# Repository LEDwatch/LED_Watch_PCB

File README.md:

# LED_Watch_PCB
LED Wrist Watch schematic and circuit board files

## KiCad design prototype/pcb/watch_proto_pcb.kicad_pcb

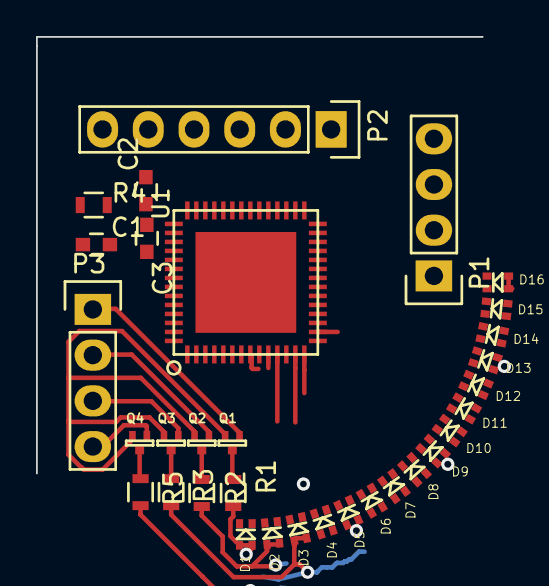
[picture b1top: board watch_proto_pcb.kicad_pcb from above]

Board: 2 copper layers, 32 parts (0 on the bottom side), 27 nets.

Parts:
C1, C2, C3: C; C_0603
D1, D2, D3, D4, D5, D6, D7, D8, D9, D10, D11, D12, D13, D14, D15, D16: APHB1608LVBDSEKJ3C; led_dual
P1, P3: CONN_01X04; Pin_Header_Straight_1x04
P2: CONN_01X06; Pin_Header_Straight_1x06
Q1, Q2, Q3, Q4: RZM001P02; SOT-723-3
R1, R2, R3, R4, R5: R; R_0603
U1: TLC5954; QFN_N56_THERM

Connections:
/proto_TLC/B0: D1.1, D2.1, D3.1, D4.1, U1.10
/proto_TLC/B1: D5.1, D6.1, D7.1, D8.1, U1.13
/proto_TLC/B2: D9.1, D10.1, D11.1, D12.1, U1.16
/proto_TLC/B3: D13.1, D14.1, D15.1, D16.1, U1.19
/proto_TLC/BLANK: P1.4, U1.29
/proto_TLC/LAT: P1.2, U1.27
/proto_TLC/LED_EN_0: P3.1, Q1.1
/proto_TLC/LED_EN_1: P3.2, Q2.1
/proto_TLC/LED_EN_2: P3.3, Q3.1
/proto_TLC/LED_EN_3: P3.4, Q4.1
/proto_TLC/LED_MOS_0: Q1.3, R1.1
/proto_TLC/LED_MOS_1: Q2.3, R2.1
/proto_TLC/LED_MOS_2: Q3.3, R3.1
/proto_TLC/LED_MOS_3: Q4.3, R5.1
/proto_TLC/LED_PWR_OUT_0: D1.2, D1.4, D5.2, D5.4, D9.2, D9.4, D13.2, D13.4, R1.2
/proto_TLC/LED_PWR_OUT_1: D2.2, D2.4, D6.2, D6.4, D10.2, D10.4, D14.2, D14.4, R2.2
/proto_TLC/LED_PWR_OUT_2: D3.2, D3.4, D7.2, D7.4, D11.2, D11.4, D15.2, D15.4, R3.2
/proto_TLC/LED_PWR_OUT_3: D4.2, D4.4, D8.2, D8.4, D12.2, D12.4, D16.2, D16.4, R5.2
/proto_TLC/R0: D1.3, D2.3, D3.3, D4.3, U1.8
/proto_TLC/R1: D5.3, D6.3, D7.3, D8.3, U1.11
/proto_TLC/R2: D9.3, D10.3, D11.3, D12.3, U1.14
/proto_TLC/R3: D13.3, D14.3, D15.3, D16.3, U1.17
/proto_TLC/SCLK: P1.3, U1.28
/proto_TLC/SIN: P1.1, U1.26
/proto_TLC/TLC_PWR: C2.1, C3.1, R4.1, U1.43
GND: C1.2, C2.2, C3.2, P2.1, P2.2, P2.3, P2.4, U1.1, U1.56, U1.57
VDD: C1.1, P2.5, P2.6, Q1.2, Q2.2, Q3.2, Q4.2, R4.2

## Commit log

2016-05-31 First Schematic files with hieracrhy
2016-05-31 Added libraries folder with TLC component
2016-05-31 Relative library path
2016-05-31 Added watch_led component library
2016-05-31 Made part number invisible
2016-06-01 Added leds to the schematic files
2016-06-01 Added pmos component
2016-06-01 Added TLC, LEDs, and bus lines
2016-06-01 Added connectors, power mosfets, hierarchial pins
2016-06-01 Generate schematic pdf
2016-06-01 Bulk caps for TLC / LEDs
2016-06-02 Finished footprints and netlist
2016-06-02 Finished rectangular prototype board
2016-06-04 Added concentric power traces
2017-04-23 Created library components for LEDs, MCU, MOSFET, and some resistors
2017-04-23 Created schematic files USES REVERSED LEDS!
2017-05-03 Added all leds, 3.3Vreg, and routed busses
